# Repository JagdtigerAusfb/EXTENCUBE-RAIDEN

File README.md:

# EXTENCUBE-RAIDEN

**[WORK IN PROGRESS]**

This repository contains everything related to the Rubik's Cube solving robot, Raiden. This project was developed as an extension project at the State University of Campinas (UNICAMP).

## Introduction

The goal of this project was to develop a simple Rubik's Cube solving robot using accessible, easy-to-use, and relatively inexpensive components. 

See a video of the completed robot in action below: 

[Insert Video Link Here]

## Documentation & Guides

* Read the **[User's Manual]** for a full description of the parts, the complete bill of materials, and relevant technical documentation.
* Read the **[Build Tutorial]** for a step-by-step guide on how to build and configure this project yourself.

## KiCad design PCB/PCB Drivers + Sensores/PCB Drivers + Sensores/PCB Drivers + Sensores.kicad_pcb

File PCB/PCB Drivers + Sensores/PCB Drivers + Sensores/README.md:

## Drivers & Sensors Shield

This board functions as a custom shield for the **Arduino Mega**. It integrates everything needed to control the mechanics and inputs of the project:
* **6x A4988 Stepper Motor Drivers**
* **12x Color Sensor Connectors**
* **1x Multiplexer** (to handle the sensor inputs)

## Power Supply & Distribution

The system is powered by a 12V power supply with two output ports. **We strongly advise using both ports.** During testing, relying on a single port caused voltage drops, which resulted in some motors stalling. 

To distribute the current load evenly, the board features **two DC Jack connectors**. Each jack supplies 12V to a dedicated group of three motor drivers.

## A4988 Drivers

**Pin configuration:**

| Driver | DIR Pin | STEP Pin | ENABLE Pin |
| :--- | :---: | :---: | :---: |
| **Driver 1** | A0 | A1 | A2 |
| **Driver 2** | A3 | A4 | A5 |
| **Driver 3** | A6 | A7 | A8 |
| **Driver 4** | 53 | 51 | 49 |
| **Driver 5** | 43 | 41 | 39 |
| **Driver 6** | 29 | 27 | 25 |

Note that these are based on what was easiest to route on the board physicaly.

In this project, we only utilize the **DIR**, **STEP**, and **EN** (Enable) pins of the motor drivers. The configuration for the remaining pins is as follows:

* **Microstepping (MS Pins):** These pins are left disconnected.
* **RESET & SLEEP Pins:** These pins are tied together. 

This specific setup is possible because the drivers used in this project include internal **pull-up or pull-down resistors**, which stabilize the signals even when left unconnected. 

> [!CAUTION]
> These pins are not accessible in the current board design. If you decide to use a different or "equivalent" driver, ensure it also features internal pull-up/down resistors. Some simpler or cheaper versions of these drivers lack these resistors; in such cases, the pins **cannot** be left floating (unconnected), or the driver will not function correctly.

## Multiplexer (CD74HC4067) and Sensors (TCS34725)

### Sensors (TCS34725)

**Pin configuration:**

| Sensor | Pino do Arduino (LED Control) |
| :--- | :---: |
| **Sensor 1** | **13** |
| **Sensor 2** | **12** |
| **Sensor 3** | **11** |
| **Sensor 4** | **10** |
| **Sensor 5** | **9** |
| **Sensor 6** | **8** |
| **Sensor 7** | **14** |
| **Sensor 8** | **15** |
| **Sensor 9** | **16** |
| **Sensor 10** | **17** |
| **Sensor 11** | **18** |
| **Sensor 12** | **19** |

In this project, we only utilize the **VIN**, **GND**, **SDA**, **SCL**, and **LED** pins of the TCS34725 color sensors. The configuration for the remaining pins is as follows:

* **Interrupt (INT Pin):** This pin is left disconnected. 
* **3.3V Pin:** This pin is also left disconnected.

> [!NOTE]
> This configuration assumes you are using a standard TCS34725 breakout module (like the ones from Adafruit or similar clones) that includes a built-in voltage regulator and I2C pull-up resistors. If you are using a different, 3.3V-only version of the board, do not connect 5V to the power pins, as it will damage the sensor!

Note that these are based on what was easiest to route on the board physicaly.

## Multiplexer (CD74HC4067)

| Pino do MUX | Pino do Arduino (Mux Control) |
| :--- | :---: |
| **S0 (LSB)** | **5** |
| **S1** | **4** |
| **S2** | **3** |
| **S3 (MSB)** | **2** |

| Sinal SDA (Sensor) | Pino do Header | Entrada do MUX |
| :--- | :---: | :---: |
| **SDA_1** | JP1-1 | **C0** |
| **SDA_2** | JP1-2 | **C1** |
| **SDA_3** | JP1-3 | **C2** |
| **SDA_4** | JP1-4 | **C3** |
| **SDA_5** | JP1-5 | **C4** |
| **SDA_6** | JP1-6 | **C5** |
| **SDA_7** | JP1-7 | **C6** |
| **SDA_8** | JP1-8 | **C7** |
| **SDA_9** | JP1-9 | **C8** |
| **SDA_10** | JP1-10 | **C9** |
| **SDA_11** | JP1-11 | **C10** |
| **SDA_12** | JP1-12 | **C11** |
| *Not Connected* | JP1-13 | **C12** |
| *Not Connected* | JP1-14 | **C13** |
| *Not Connected* | JP1-15 | **C14** |
| *Not Connected* | JP1-16 | **C15** |

## Optional Components

 **Indicator LEDs:** There are LEDs (and their corresponding resistors) to indicate power from the two 12V jacks and the 5V line from the Arduino. Additionally, each A4988 driver has a dedicated LED to show when a step signal is being sent to the motor. You can safely exclude these if you prefer. 
 
 **Reset Button:** The board includes a physical Reset button for the Arduino. This can also be omitted.
 
 **Highly Recommended - Capacitors:** While the board might technically work without them, installing the decoupling capacitors for the motor drivers is **highly recommended**. They are crucial for preventing voltage spikes that can permanently damage the A4988 drivers.

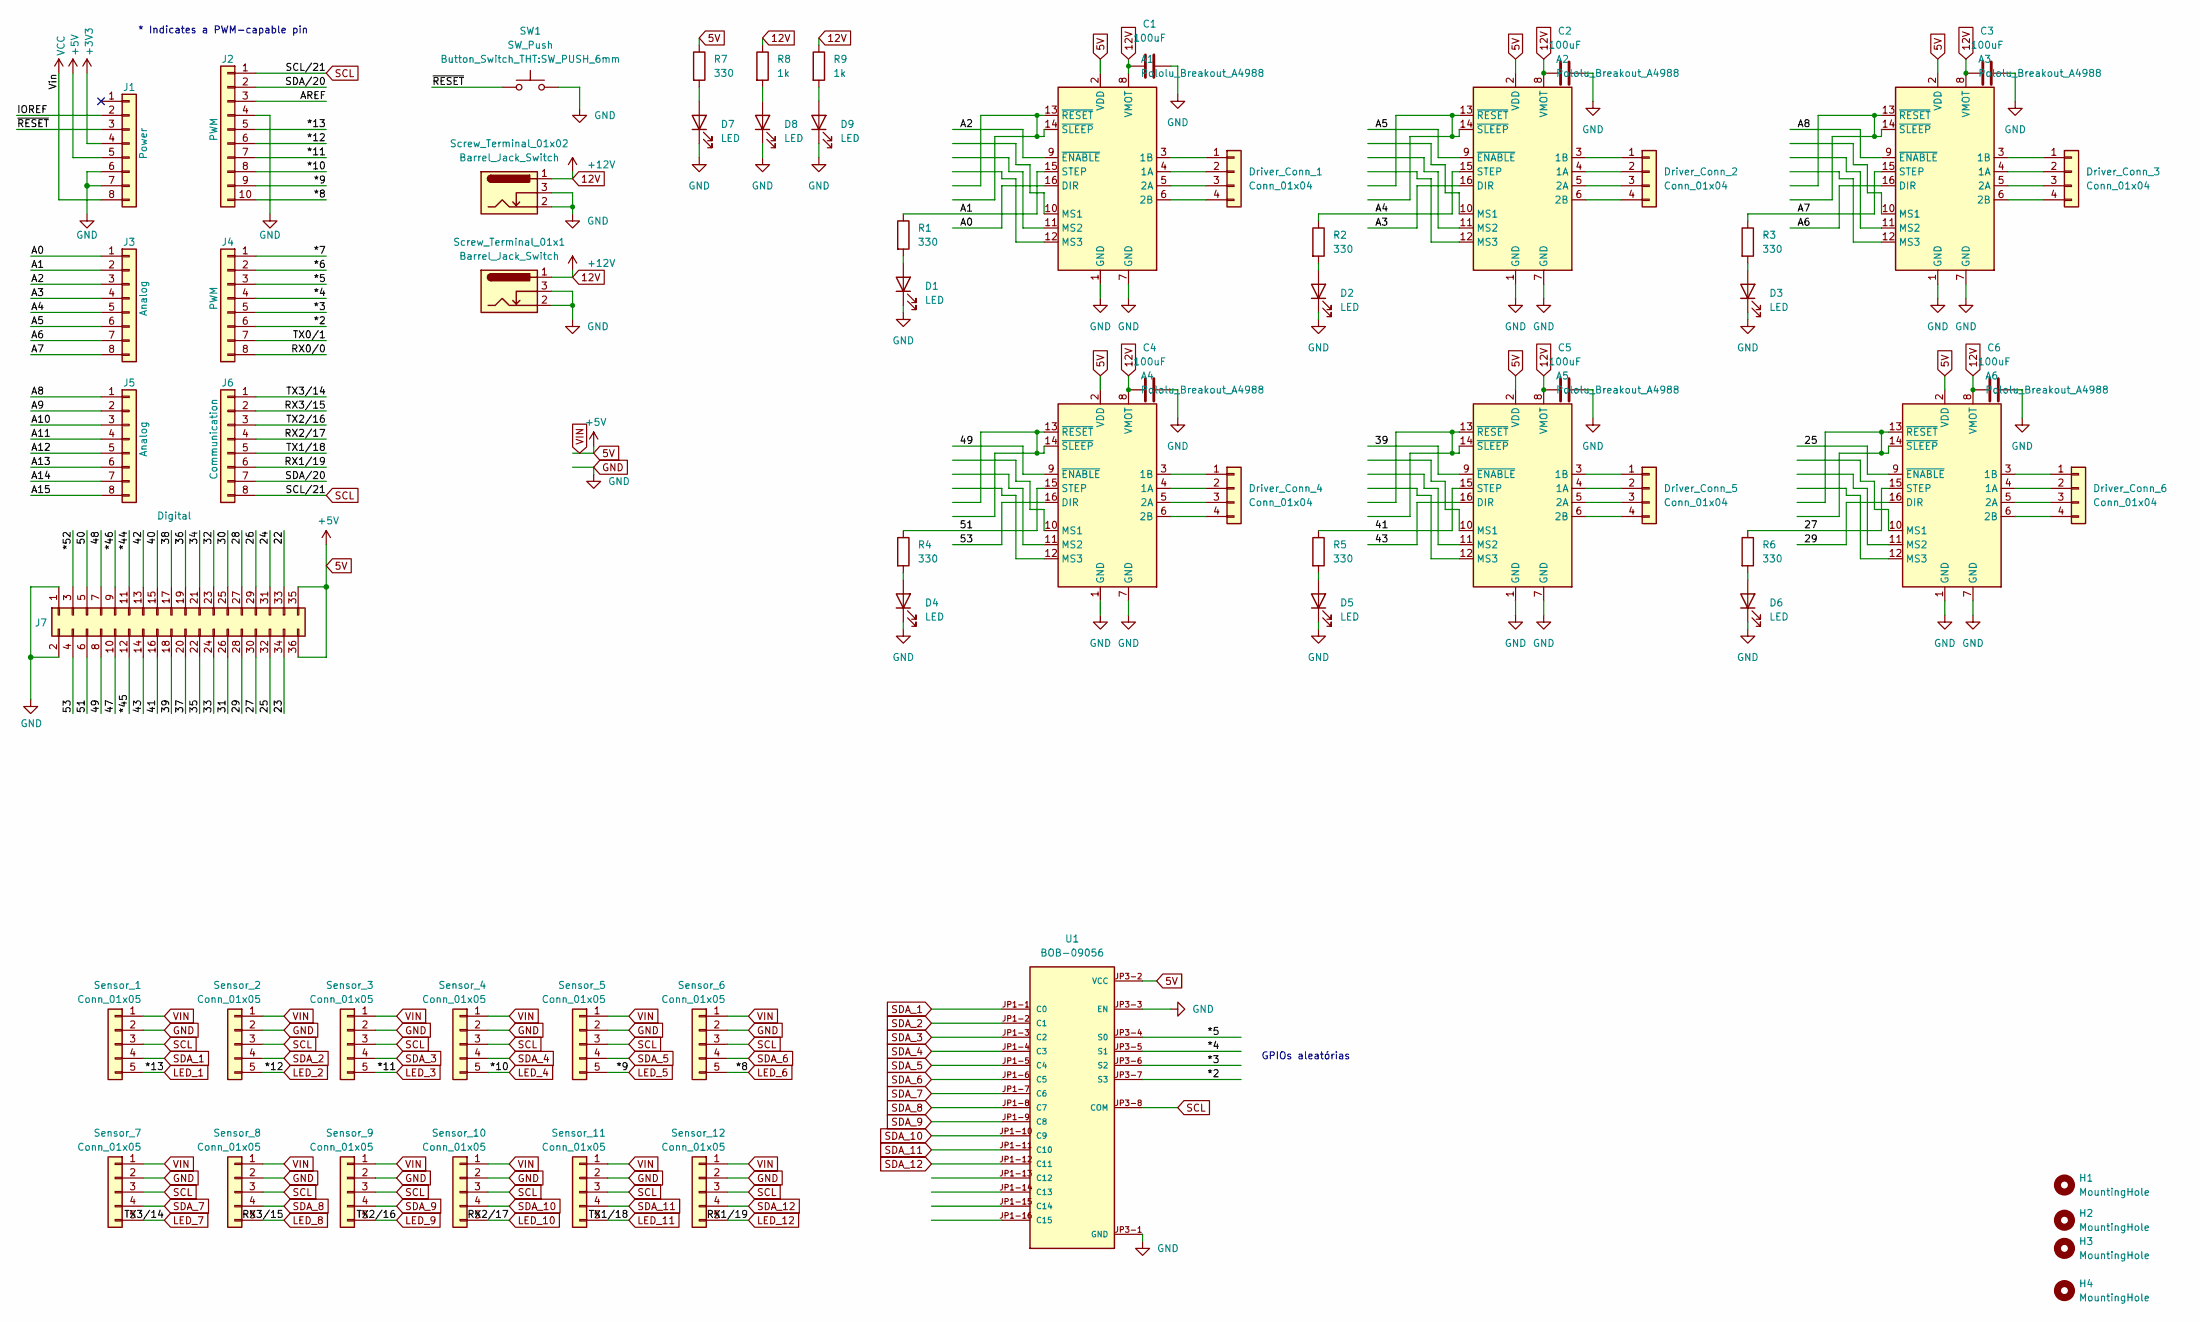
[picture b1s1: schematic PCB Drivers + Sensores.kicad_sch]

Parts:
A1, A2, A3, A4, A5, A6: Pololu_Breakout_A4988; Pololu_Breakout-16_15.2x20.3mm
C1, C2, C3, C4, C5, C6: 100uF; CP_Radial_D8.0mm_P3.50mm
D1, D2, D3, D4, D5, D6, D7, D8, D9: LED; LED_D5.0mm
Driver_Conn_1, Driver_Conn_2, Driver_Conn_3, Driver_Conn_4, Driver_Conn_5, Driver_Conn_6: Conn_01x04; JST_XH_B4B-XH-A_1x04_P2.50mm_Vertical
H1, H2, H3, H4: MountingHole; MountingHole_6mm
J1: Power; PinSocket_1x08_P2.54mm_Vertical
J2: PWM; PinSocket_1x10_P2.54mm_Vertical
J3, J5: Analog; PinSocket_1x08_P2.54mm_Vertical
J4: PWM; PinSocket_1x08_P2.54mm_Vertical
J6: Communication; PinSocket_1x08_P2.54mm_Vertical
J7: Digital; PinSocket_2x18_P2.54mm_Vertical
R1, R2, R3, R4, R5, R6, R7: 330; R_Axial_DIN0207_L6.3mm_D2.5mm_P10.16mm_Horizontal
R8, R9: 1k; R_Axial_DIN0207_L6.3mm_D2.5mm_P10.16mm_Horizontal
SW1: SW_Push; SW_PUSH_6mm
Screw_Terminal_01x1, Screw_Terminal_01x02: Barrel_Jack_Switch; BarrelJack_Horizontal
Sensor_1, Sensor_2, Sensor_3, Sensor_4, Sensor_5, Sensor_6, Sensor_7, Sensor_8, Sensor_9, Sensor_10, Sensor_11, Sensor_12: Conn_01x05; JST_XH_B5B-XH-A_1x05_P2.50mm_Vertical
U1: BOB-09056; MODULE_BOB-09056; PARTREV v11

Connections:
5V: A1.2 (VDD), A2.2 (VDD), A3.2 (VDD), A4.2 (VDD), A5.2 (VDD), A6.2 (VDD), J1.5, J7.35, J7.36, R7.1, Sensor_1.1, Sensor_2.1, Sensor_3.1, Sensor_4.1, Sensor_5.1, Sensor_6.1, Sensor_7.1, Sensor_8.1, Sensor_9.1, Sensor_10.1, Sensor_11.1, Sensor_12.1, U1.JP3-2 (VCC)
12V: A1.8 (VMOT), A2.8 (VMOT), A3.8 (VMOT), A4.8 (VMOT), A5.8 (VMOT), A6.8 (VMOT), C1.1, C2.1, C3.1, C4.1, C5.1, C6.1, R8.1, R9.1, Screw_Terminal_01x1.1, Screw_Terminal_01x02.1
+3V3: J1.4
/22: J7.33
/23: J7.34
/24: J7.31
/25: A6.9 (~ENABLE), J7.32
/26: J7.29
/27: A6.15 (STEP), J7.30, R6.1
/28: J7.27
/29: A6.16 (DIR), J7.28
/30: J7.25
/31: J7.26
/32: J7.23
/33: J7.24
/34: J7.21
/35: J7.22
/36: J7.19
/37: J7.20
/38: J7.17
/39: A5.9 (~ENABLE), J7.18
/40: J7.15
/41: A5.15 (STEP), J7.16, R5.1
/42: J7.13
/43: A5.16 (DIR), J7.14
/47: J7.10
/48: J7.7
/49: A4.9 (~ENABLE), J7.8
/50: J7.5
/51: A4.15 (STEP), J7.6, R4.1
/53: A4.16 (DIR), J7.4
/*2: J4.6, U1.JP3-7 (S3)
/*3: J4.5, U1.JP3-6 (S2)
/*4: J4.4, U1.JP3-5 (S1)
/*5: J4.3, U1.JP3-4 (S0)
/*6: J4.2
/*7: J4.1
/*44: J7.11
/*45: J7.12
/*46: J7.9
/*52: J7.3
/A0: A1.16 (DIR), J3.1
/A1: A1.15 (STEP), J3.2, R1.1
/A2: A1.9 (~ENABLE), J3.3
/A3: A2.16 (DIR), J3.4
/A4: A2.15 (STEP), J3.5, R2.1
/A5: A2.9 (~ENABLE), J3.6
/A6: A3.16 (DIR), J3.7
/A7: A3.15 (STEP), J3.8, R3.1
/A8: A3.9 (~ENABLE), J5.1
/A9: J5.2
/A10: J5.3
/A11: J5.4
/A12: J5.5
/A13: J5.6
/A14: J5.7
/A15: J5.8
/AREF: J2.3
/IOREF: J1.2
/RX0/0: J4.8
/SDA/20: J2.2, J6.7
/TX0/1: J4.7
/~RESET: J1.3, SW1.1
GND: A1.1 (GND), A1.7 (GND), A2.1 (GND), A2.7 (GND), A3.1 (GND), A3.7 (GND), A4.1 (GND), A4.7 (GND), A5.1 (GND), A5.7 (GND), A6.1 (GND), A6.7 (GND), C1.2, C2.2, C3.2, C4.2, C5.2, C6.2, D1.1 (K), D2.1 (K), D3.1 (K), D4.1 (K), D5.1 (K), D6.1 (K), D7.1 (K), D8.1 (K), D9.1 (K), J1.6, J1.7, J2.4, J7.1, J7.2, SW1.2, Screw_Terminal_01x1.2, Screw_Terminal_01x1.3, Screw_Terminal_01x02.2, Screw_Terminal_01x02.3, Sensor_1.2, Sensor_2.2, Sensor_3.2, Sensor_4.2, Sensor_5.2, Sensor_6.2, Sensor_7.2, Sensor_8.2, Sensor_9.2, Sensor_10.2, Sensor_11.2, Sensor_12.2, U1.JP3-1 (GND), U1.JP3-3 (EN)
LED_1: J2.5, Sensor_1.5
LED_2: J2.6, Sensor_2.5
LED_3: J2.7, Sensor_3.5
LED_4: J2.8, Sensor_4.5
LED_5: J2.9, Sensor_5.5
LED_6: J2.10, Sensor_6.5
LED_7: J6.1, Sensor_7.5
LED_8: J6.2, Sensor_8.5
LED_9: J6.3, Sensor_9.5
LED_10: J6.4, Sensor_10.5
LED_11: J6.5, Sensor_11.5
LED_12: J6.6, Sensor_12.5
unnamed: A1.4 (1A), Driver_Conn_1.2
unnamed: A1.3 (1B), Driver_Conn_1.1
unnamed: A1.5 (2A), Driver_Conn_1.3
unnamed: A1.6 (2B), Driver_Conn_1.4
unnamed: A1.13 (~RESET), A1.14 (~SLEEP)
unnamed: A2.4 (1A), Driver_Conn_2.2
unnamed: A2.3 (1B), Driver_Conn_2.1
unnamed: A2.5 (2A), Driver_Conn_2.3
unnamed: A2.6 (2B), Driver_Conn_2.4
unnamed: A2.13 (~RESET), A2.14 (~SLEEP)
unnamed: A3.4 (1A), Driver_Conn_3.2
unnamed: A3.3 (1B), Driver_Conn_3.1
unnamed: A3.5 (2A), Driver_Conn_3.3
unnamed: A3.6 (2B), Driver_Conn_3.4
unnamed: A3.13 (~RESET), A3.14 (~SLEEP)
unnamed: A4.4 (1A), Driver_Conn_4.2
unnamed: A4.3 (1B), Driver_Conn_4.1
unnamed: A4.5 (2A), Driver_Conn_4.3
unnamed: A4.6 (2B), Driver_Conn_4.4
unnamed: A4.13 (~RESET), A4.14 (~SLEEP)
unnamed: A5.4 (1A), Driver_Conn_5.2
unnamed: A5.3 (1B), Driver_Conn_5.1
unnamed: A5.5 (2A), Driver_Conn_5.3
unnamed: A5.6 (2B), Driver_Conn_5.4
unnamed: A5.13 (~RESET), A5.14 (~SLEEP)
unnamed: A6.4 (1A), Driver_Conn_6.2
unnamed: A6.3 (1B), Driver_Conn_6.1
unnamed: A6.5 (2A), Driver_Conn_6.3
unnamed: A6.6 (2B), Driver_Conn_6.4
unnamed: A6.13 (~RESET), A6.14 (~SLEEP)
unnamed: D1.2 (A), R1.2
unnamed: D2.2 (A), R2.2
unnamed: D3.2 (A), R3.2
unnamed: D4.2 (A), R4.2
unnamed: D5.2 (A), R5.2
unnamed: D6.2 (A), R6.2
unnamed: D7.2 (A), R7.2
unnamed: D8.2 (A), R8.2
unnamed: D9.2 (A), R9.2
SCL: J2.1, J6.8, Sensor_1.3, Sensor_2.3, Sensor_3.3, Sensor_4.3, Sensor_5.3, Sensor_6.3, Sensor_7.3, Sensor_8.3, Sensor_9.3, Sensor_10.3, Sensor_11.3, Sensor_12.3, U1.JP3-8 (COM)
SDA_1: Sensor_1.4, U1.JP1-1 (C0)
SDA_2: Sensor_2.4, U1.JP1-2 (C1)
SDA_3: Sensor_3.4, U1.JP1-3 (C2)
SDA_4: Sensor_4.4, U1.JP1-4 (C3)
SDA_5: Sensor_5.4, U1.JP1-5 (C4)
SDA_6: Sensor_6.4, U1.JP1-6 (C5)
SDA_7: Sensor_7.4, U1.JP1-7 (C6)
SDA_8: Sensor_8.4, U1.JP1-8 (C7)
SDA_9: Sensor_9.4, U1.JP1-9 (C8)
SDA_10: Sensor_10.4, U1.JP1-10 (C9)
SDA_11: Sensor_11.4, U1.JP1-11 (C10)
SDA_12: Sensor_12.4, U1.JP1-12 (C11)
VCC: J1.8

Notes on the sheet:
GPIOs aleatórias
* Indicates a PWM-capable pin

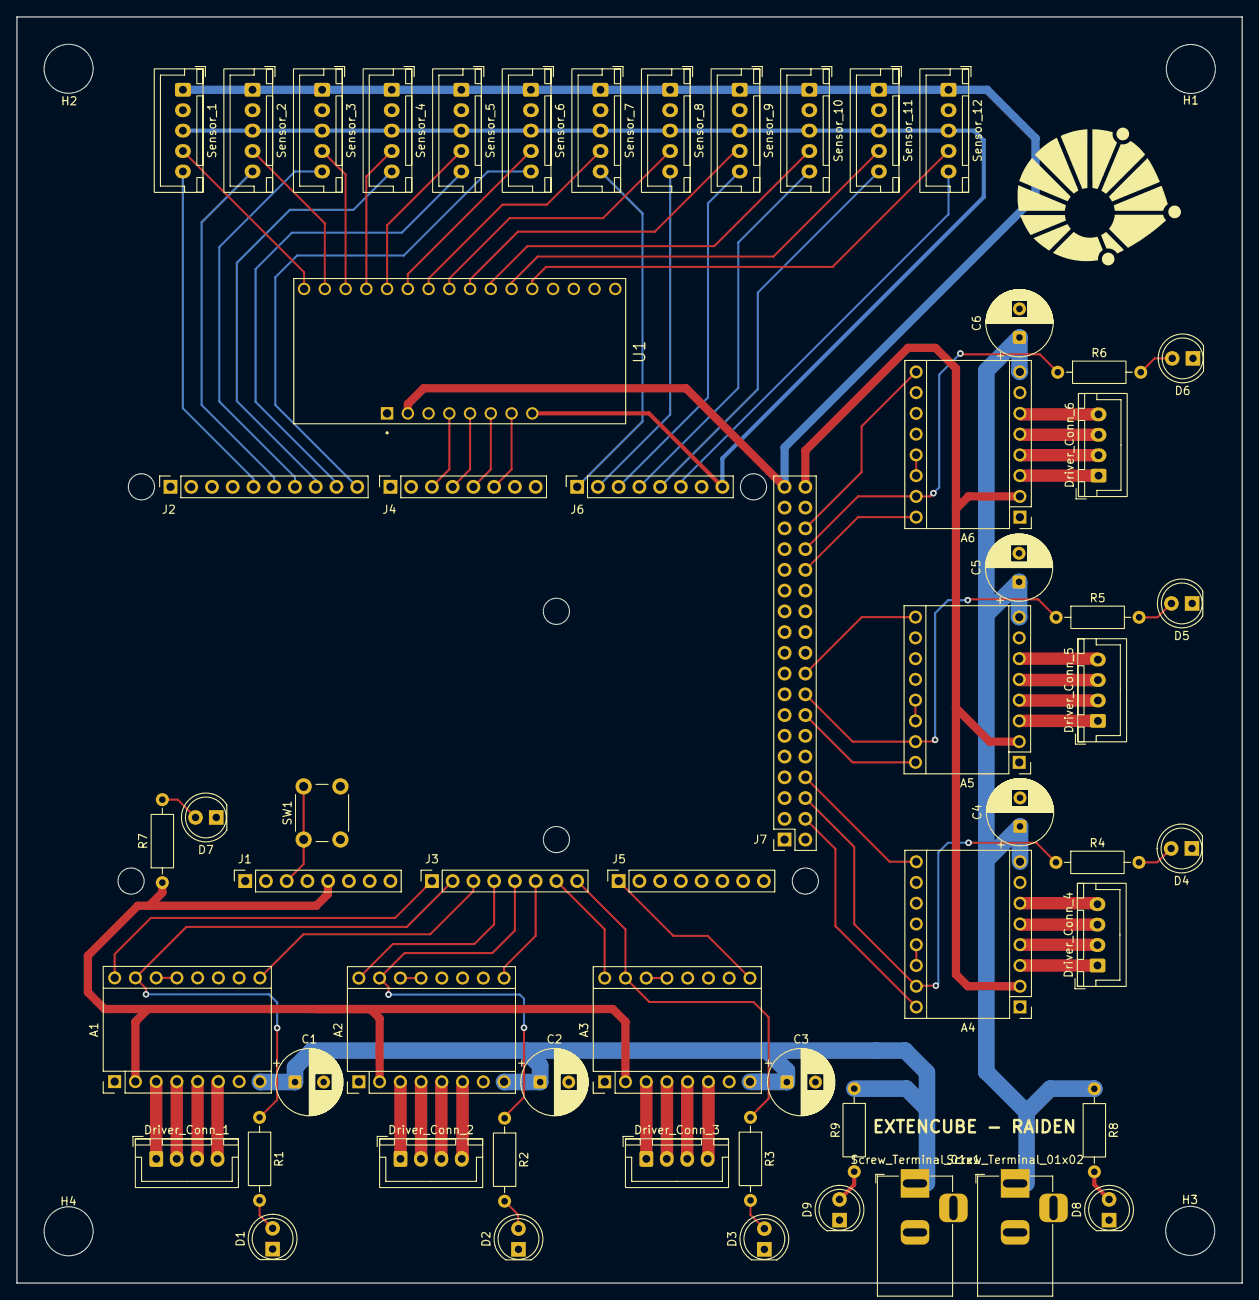
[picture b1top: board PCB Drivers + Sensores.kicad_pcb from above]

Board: 2 copper layers, 150.0 x 155.0 mm, 69 parts (0 on the bottom side), 91 nets.

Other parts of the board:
MH1, MH2, MH3, MH4, MH5, MH6: MountingHole_3.2mm

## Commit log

2026-03-16 First Files - PCB
2026-03-17 Primeiro Modelo
2026-03-18 Multplex + Sensores
2026-03-18 Versáo Teste - Trilhas Menores
2026-03-19 Versão Final - V1
2026-03-19 Placa Final - +Leds +Botão
2026-03-19 Arquivos inúteis excluidos
2026-03-19 Pasta de Softwares
2026-03-19 Teste
2026-03-19 Arquivos da PCB de drivers
2026-03-19 Rename image.md to README.md
2026-03-19 Gerbers
2026-03-19 +LEDs, +BARREL JACK
2026-03-20 Logos no Silkscreen
2026-03-20 3D file
2026-03-23 Nova UI
2026-03-23 UI segunda versão
2026-03-23 UI V3
2026-03-23 UI V4 - Nome e imagem do app
2026-03-23 UI final + problema do motor identificado
2026-03-25 Relative Path to files added
2026-03-25 README update
2026-03-27 "m2op" concerto de bugs
2026-03-28 Create Cube_3D
2026-03-28 cube3D código
2026-03-30 Embaralhamento de 19 moves
    Se quebrou algo, reverta esse comit
2026-03-31 Caminho relativo do json do cubo 3D
2026-04-09 Clarify motor pin definitions with comments
    Added comments to clarify motor pin definitions.
2026-04-09 Fix comments for motor direction pin definitions
2026-04-10 cube3D + full organization
2026-04-10 debug
2026-04-10 FullScreen + Novos Pinos no Arduino + Eixo de coordenadas
2026-04-10 bug fixes
2026-04-10 setting (S) improve
2026-04-10 Códigos de Teste
2026-04-10 add interface features
2026-05-05 Funcionando?
2026-05-16 PCB tupan
